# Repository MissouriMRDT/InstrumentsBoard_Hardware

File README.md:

# InstrumentsBoard_Hardware
Control board for science instruments, including the Raman spectrometer and reflectance spectrometer

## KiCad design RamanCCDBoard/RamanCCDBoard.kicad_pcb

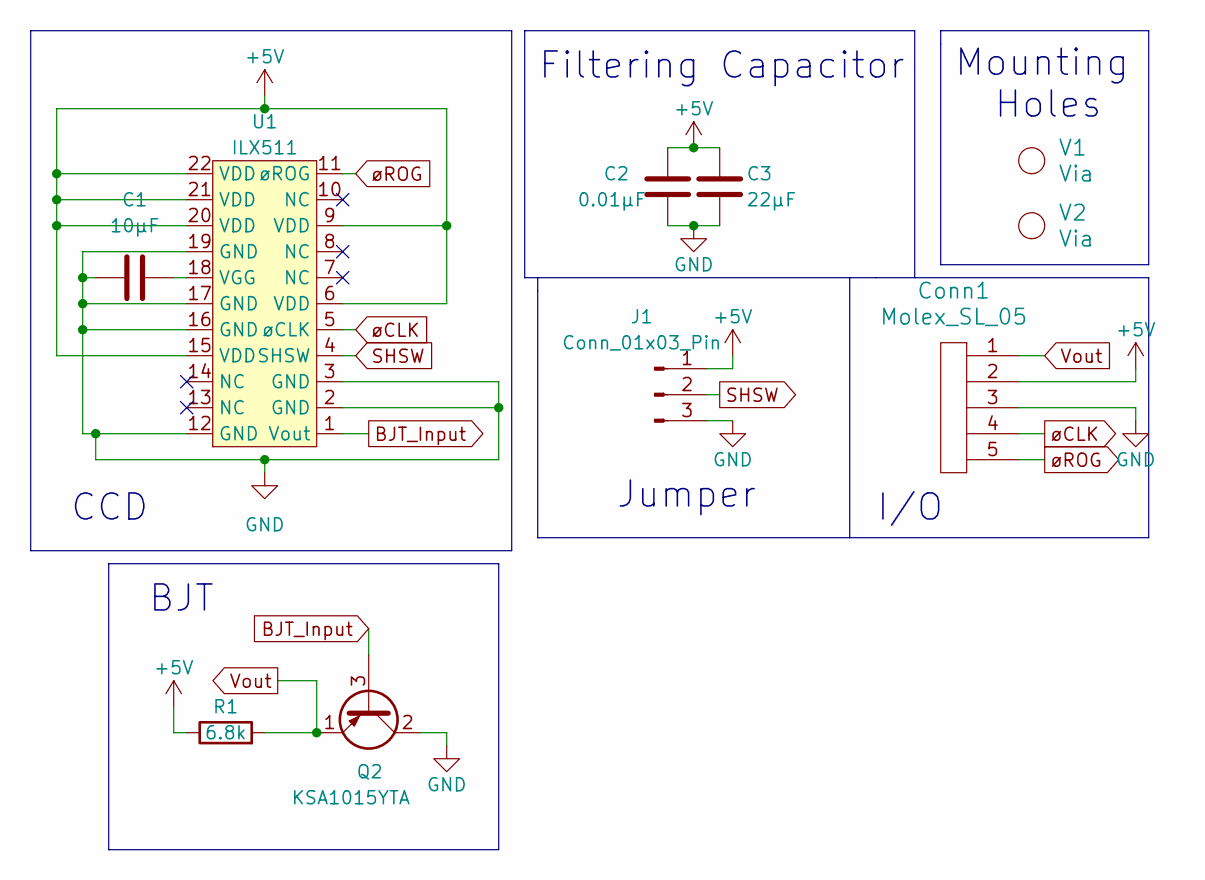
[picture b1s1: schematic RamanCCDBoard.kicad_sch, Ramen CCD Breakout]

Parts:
C1: 10µF; C_0603_1608Metric_Pad1.08x0.95mm_HandSolder
C2: 0.01µF; C_0603_1608Metric_Pad1.08x0.95mm_HandSolder
C3: 22µF; C_0603_1608Metric_Pad1.08x0.95mm_HandSolder
Conn1: Molex_SL_05; MOLEX_SL_05_Vertical
J1: Conn_01x03_Pin; PinHeader_1x03_P2.54mm_Vertical
Q2: KSA1015YTA; TO-92_Inline
R1: 6.8k; R_0603_1608Metric_Pad0.98x0.95mm_HandSolder
U1: ILX511
V1, V2: Via; 4_40_Hole

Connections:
+5V: C2.2, C3.2, Conn1.2, J1.1, R1.1, U1.6 (VDD), U1.9 (VDD), U1.15 (VDD), U1.20 (VDD), U1.21 (VDD), U1.22 (VDD)
BJT_Input: Q2.3 (B), U1.1 (Vout)
GND: C1.1, C2.1, C3.1, Conn1.3, J1.3, Q2.2 (C), U1.2 (GND), U1.3 (GND), U1.12 (GND), U1.16 (GND), U1.17 (GND), U1.19 (GND)
unnamed: C1.2, U1.18 (VGG)
SHSW: J1.2, U1.4 (SHSW)
Vout: Conn1.1, Q2.1 (E), R1.2
øCLK: Conn1.4, U1.5 (øCLK)
øROG: Conn1.5, U1.11 (øROG)

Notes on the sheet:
Filtering Capacitor
I/O
BJT
CCD
Mounting Holes
Jumper

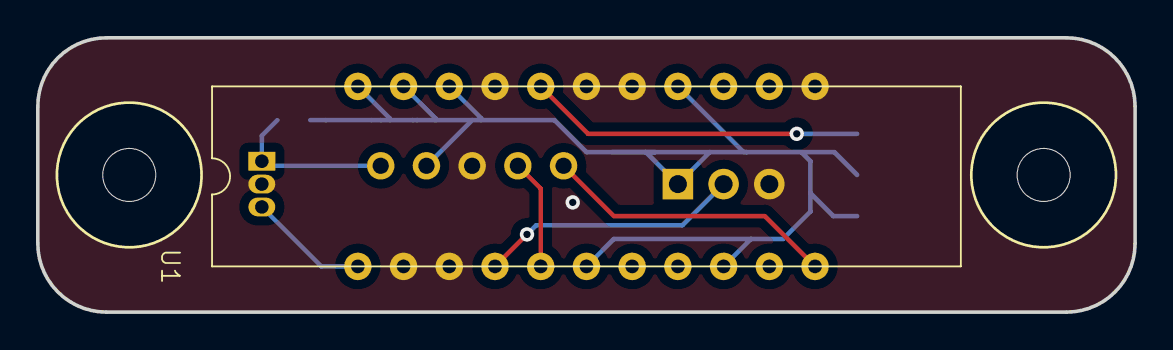
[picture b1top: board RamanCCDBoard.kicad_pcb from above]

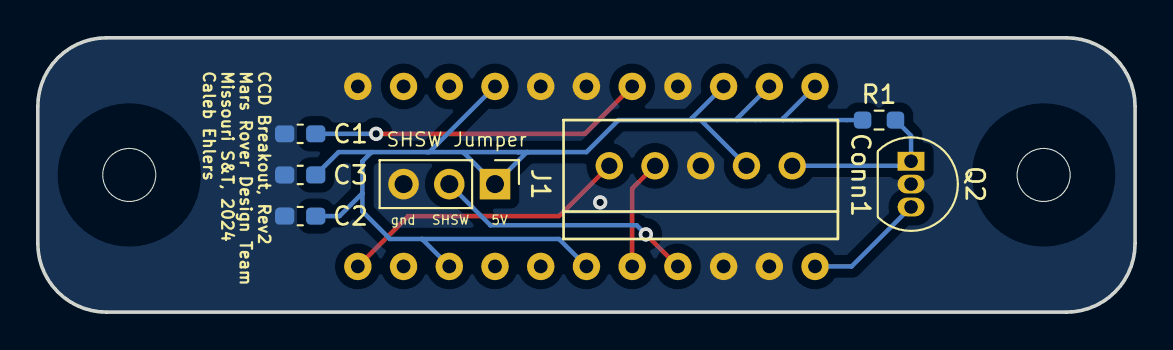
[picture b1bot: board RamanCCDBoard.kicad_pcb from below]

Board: 2 copper layers, 61.0 x 15.2 mm, 10 parts (7 on the bottom side), 8 nets.

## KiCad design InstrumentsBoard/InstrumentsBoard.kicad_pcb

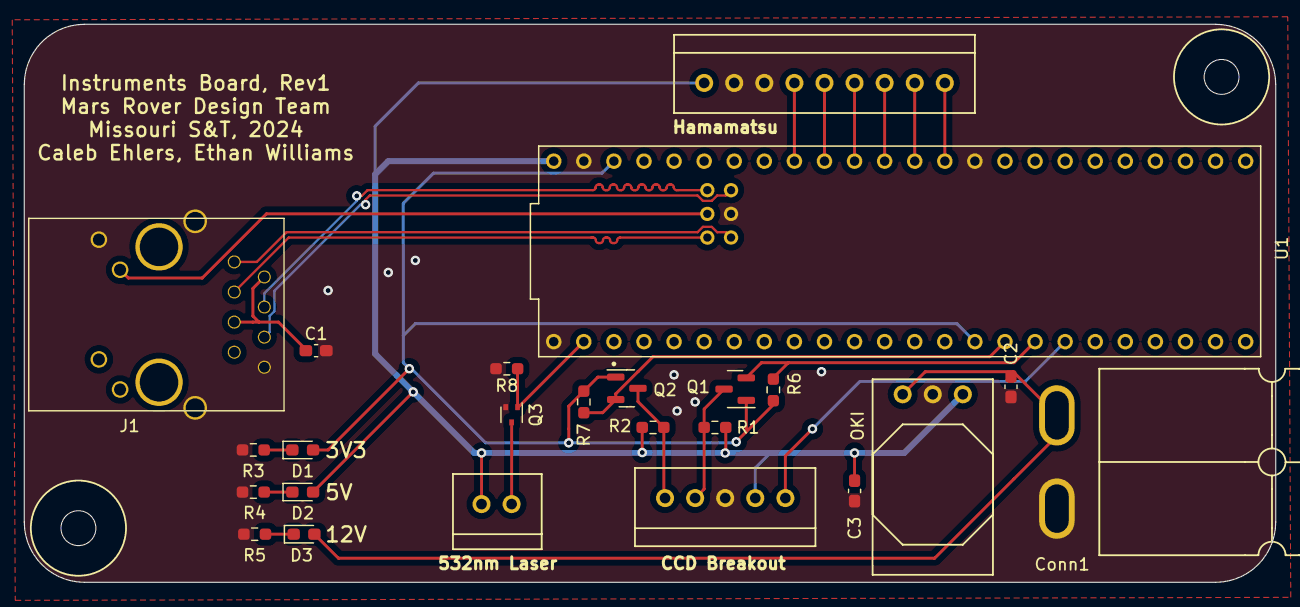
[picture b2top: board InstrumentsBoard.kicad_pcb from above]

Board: 2 copper layers, 105.7 x 47.1 mm, 26 parts (0 on the bottom side), 26 nets.

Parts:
C1: 0.1µF; C_0603_1608Metric_Pad1.08x0.95mm_HandSolder
C2, C3: 10µF; C_0603_1608Metric_Pad1.08x0.95mm_HandSolder
Conn1: AndersonPP; Square_Anderson_2_H_Side_By_Side
Conn2: Molex_SL_05; MOLEX_SL_05_Vertical
Conn4: Molex_SL_09; MOLEX_SL_09_Vertical
Conn5: Molex_SL_02; MOLEX_SL_02_Vertical
D1, D2, D3: Green; LED_0603_1608Metric_Pad1.05x0.95mm_HandSolder
J1: RJ45_LED_Shielded; RJ45_Teensy
Q1, Q2: BSS138; SOT-23
Q3: BSS138BK; SOT-523
R1, R2, R6, R7, R8: 4.7k; R_0603_1608Metric_Pad0.98x0.95mm_HandSolder
R3: 100; R_0603_1608Metric_Pad0.98x0.95mm_HandSolder
R4: 300; R_0603_1608Metric_Pad0.98x0.95mm_HandSolder
R5: 1k; R_0603_1608Metric_Pad0.98x0.95mm_HandSolder
U1: Teensy4.1_DEV-16771; Teensy_4_1_Ethernet
U2: OKI; OKI_Horizontal
V1, V2: Via; 4_40_Hole

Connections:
+3V3: D1.2 (A), Q1.1 (G), Q2.1 (G), R6.1, R7.1, U1.3.3V_1 (3.3V), U1.3.3V_2 (3.3V)
+5V: C3.1, Conn2.2, Conn4.1, Conn5.2, D2.2 (A), R1.1, R2.1, U1.VIN, U2.3 (Vo)
+12V: C2.1, Conn1.2 (V+Log), D3.2 (A), U2.1 (Vi)
CCD_CLK_3V3: Q1.2 (S), R6.2, U1.25 (A11)
CCD_CLK_5V: Conn2.4, Q1.3 (D), R1.2
CCD_ROG_3V3: Q2.2 (S), R7.2, U1.24 (A10)
CCD_ROG_5V: Conn2.5, Q2.3 (D), R2.2
CCD_Vout: Conn2.1, U1.26 (A12)
CLK: Conn4.7, U1.15 (A1)
EOS: Conn4.4, U1.18 (A4)
GND: C1.2, C2.2, C3.2, Conn1.1 (GND), Conn2.3, Conn4.2, Conn4.3, J1.8, J1.9, J1.SH, Q3.2 (S), R3.2, R4.2, R5.2, R8.2, U1.GND1 (GND), U1.GND2 (GND), U1.GND3 (GND), U1.GND5 (GND), U2.2 (GND)
Green_Laser_3V3: Q3.1 (G), R8.1, U1.0 (RX1)
LED: J1.10, U1.LED
unnamed: C1.1, J1.2, J1.5
unnamed: D1.1 (K), R3.1
unnamed: D2.1 (K), R4.1
unnamed: D3.1 (K), R5.1
unnamed: Conn5.1, Q3.3 (D)
R+: J1.4, U1.R+
R-: J1.6, U1.R-
START: Conn4.6, U1.16 (A2)
T+: J1.1, U1.T+
T-: J1.3, U1.T-
TRG: Conn4.5, U1.17 (A3)
VIDEO: Conn4.8, U1.14 (A0)
WHITE_LED: Conn4.9, U1.13 (SCK)

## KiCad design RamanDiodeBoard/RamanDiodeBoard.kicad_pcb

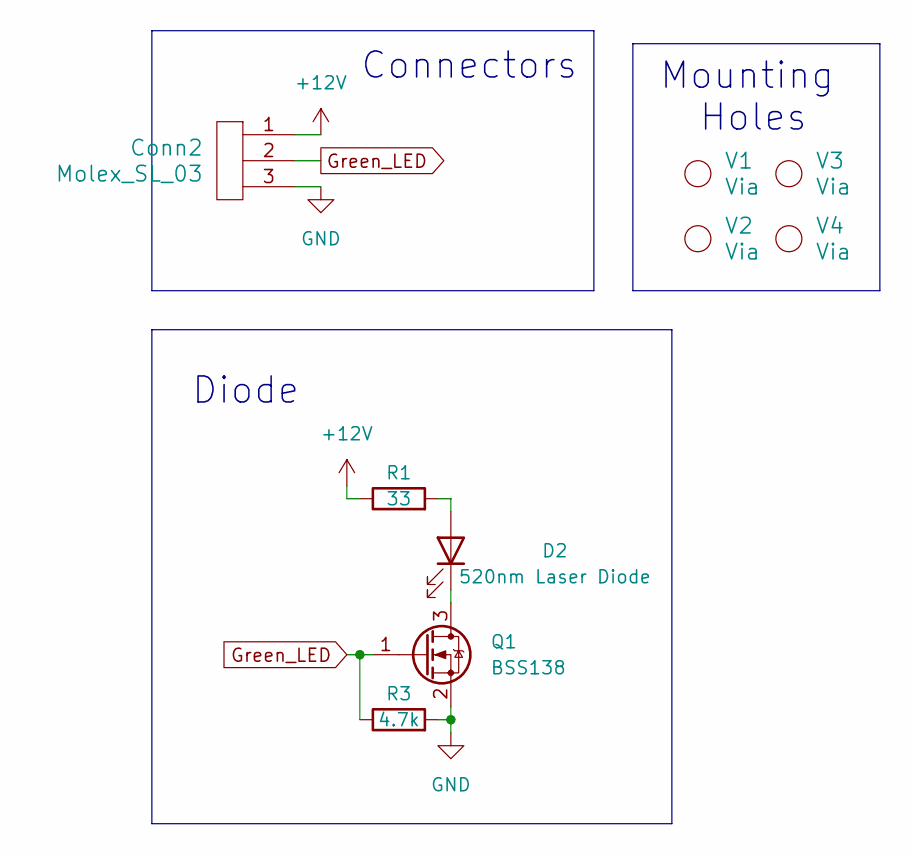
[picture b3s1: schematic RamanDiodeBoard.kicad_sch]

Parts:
Conn2: Molex_SL_03; MOLEX_SL_03_Vertical
D2: 520nm Laser Diode; PLT5520B - 520nm
Q1: BSS138; SOT-23
R1: 33; R_2512_6332Metric_Pad1.40x3.35mm_HandSolder
R3: 4.7k; R_0603_1608Metric_Pad0.98x0.95mm_HandSolder
V1, V2, V3, V4: Via; 4_40_Hole

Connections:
+12V: Conn2.1, R1.1
GND: Conn2.3, Q1.2 (S), R3.2
Green_LED: Conn2.2, Q1.1 (G), R3.1
unnamed: D2.2 (A), R1.2
unnamed: D2.1 (K), Q1.3 (D)

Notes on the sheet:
Mounting Holes
Connectors
Diode

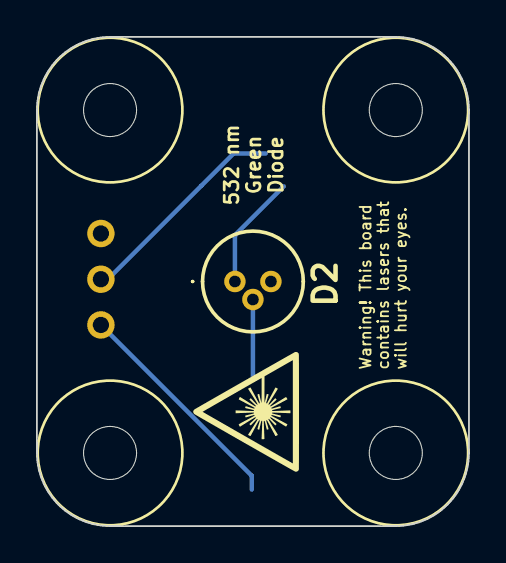
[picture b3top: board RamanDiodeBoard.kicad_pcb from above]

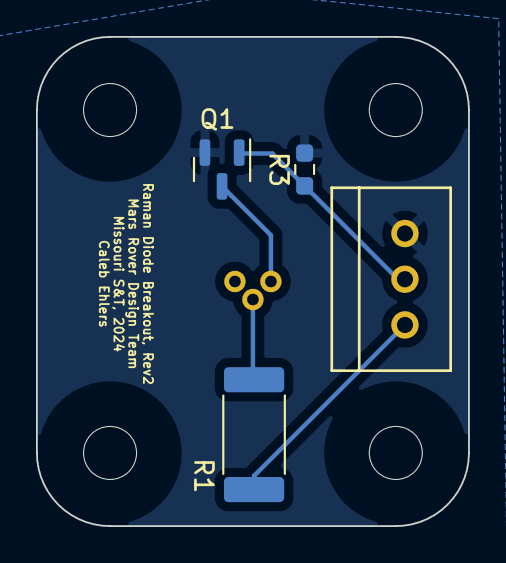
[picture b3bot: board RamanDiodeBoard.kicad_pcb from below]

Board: 2 copper layers, 24.0 x 27.2 mm, 9 parts (4 on the bottom side), 5 nets.

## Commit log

2024-03-04 commit Raman boards
2024-03-04 laser diode board changes
2024-03-05 add bjt to ccd
2024-03-05 change pin ordering for ccd molex
2024-03-05 misc cleanup
2024-03-06 Added Hamamatsu Connector, Updated Silkscreen
2024-03-07 Labeled All Pins, Shifted Teensy Over
2024-03-07 fix 5V traces
2024-03-07 remove laser diode board, add laser mosfet
2024-03-07 Fixed Hamamatsu Silkscreen
2024-03-11 revert back to laser diode board
2024-03-12 Revert "revert back to laser diode board"
    This reverts commit 6528700a9c51bf2c3bc149a74fbf2f6639f4022b.
2024-03-13 board review changes
2024-03-13 fix low side toggle circuit
2024-03-17 update laser mosfet package
2024-03-20 Bold Pin Labels
2024-03-26 generated gerbs
